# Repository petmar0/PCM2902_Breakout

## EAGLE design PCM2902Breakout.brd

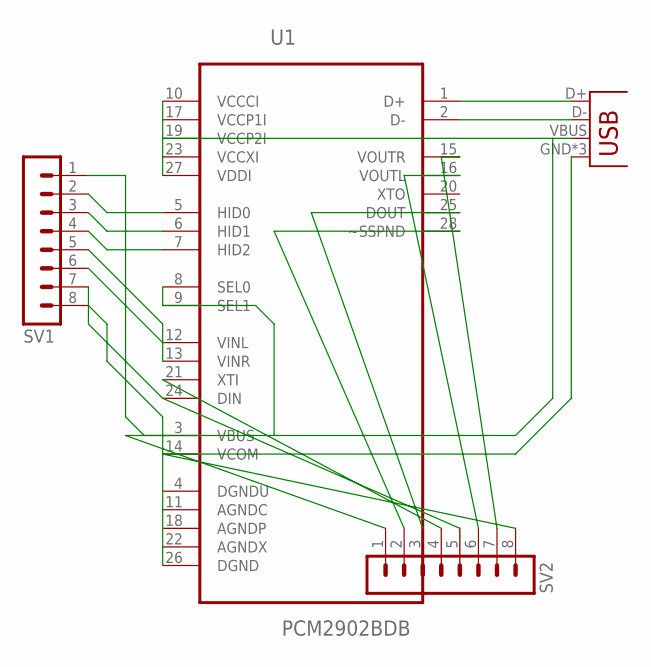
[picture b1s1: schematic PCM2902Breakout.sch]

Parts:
JP1: USB-MICROB
SV1, SV2: MA08-1
U1: PCM2902BDB; SOP65P780X200-28N

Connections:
unnamed: JP1.D+, U1.1 (D+)
unnamed: JP1.D-, U1.2 (D-)
unnamed: SV1.2, U1.5 (HID0)
unnamed: JP1.GND, JP1.MT1 (GND), JP1.MT2 (GND), SV1.8, SV2.8, U1.4 (DGNDU), U1.11 (AGNDC), U1.14 (VCOM), U1.18 (AGNDP), U1.22 (AGNDX), U1.26 (DGND)
unnamed: SV1.3, U1.6 (HID1)
unnamed: SV1.4, U1.7 (HID2)
unnamed: JP1.VBUS, SV1.1, SV2.1, U1.3 (VBUS), U1.8 (SEL0), U1.9 (SEL1), U1.10 (VCCCI), U1.17 (VCCP1I), U1.19 (VCCP2I), U1.23 (VCCXI), U1.27 (VDDI)
unnamed: SV1.5, U1.12 (VINL)
unnamed: SV1.6, U1.13 (VINR)
unnamed: SV1.7, U1.24 (DIN)
unnamed: SV2.2, U1.28 (~SSPND)
unnamed: SV2.3, U1.25 (DOUT)
unnamed: SV2.6, U1.16 (VOUTL)
unnamed: SV2.7, U1.15 (VOUTR)

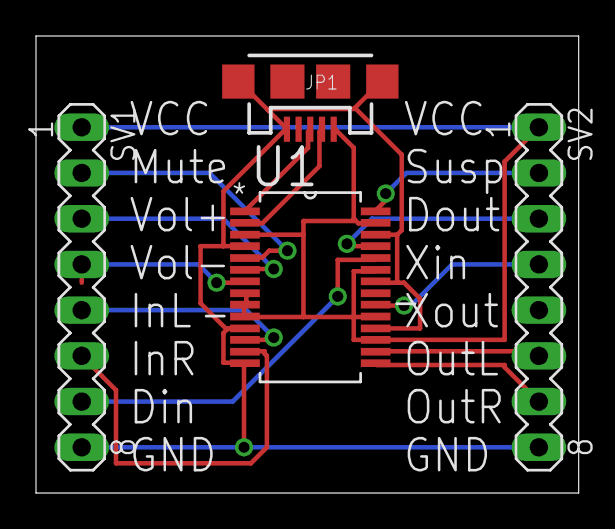
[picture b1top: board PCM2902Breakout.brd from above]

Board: 2 copper layers, 30.1 x 25.4 mm, 4 parts (0 on the bottom side), 14 nets.

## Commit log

2014-08-13 PCM2902 USB Codec Breakout Board
    Initial Commit

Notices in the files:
parts and their libraries:
SparkFun-Connectors: Licensing: CC v3.0 Share-Alike You are welcome to use this library for commercial purposes.
